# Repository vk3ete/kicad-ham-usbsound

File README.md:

# kicad-ham-usbsound
Kicad soundcard for ICOM 7100 breakboard

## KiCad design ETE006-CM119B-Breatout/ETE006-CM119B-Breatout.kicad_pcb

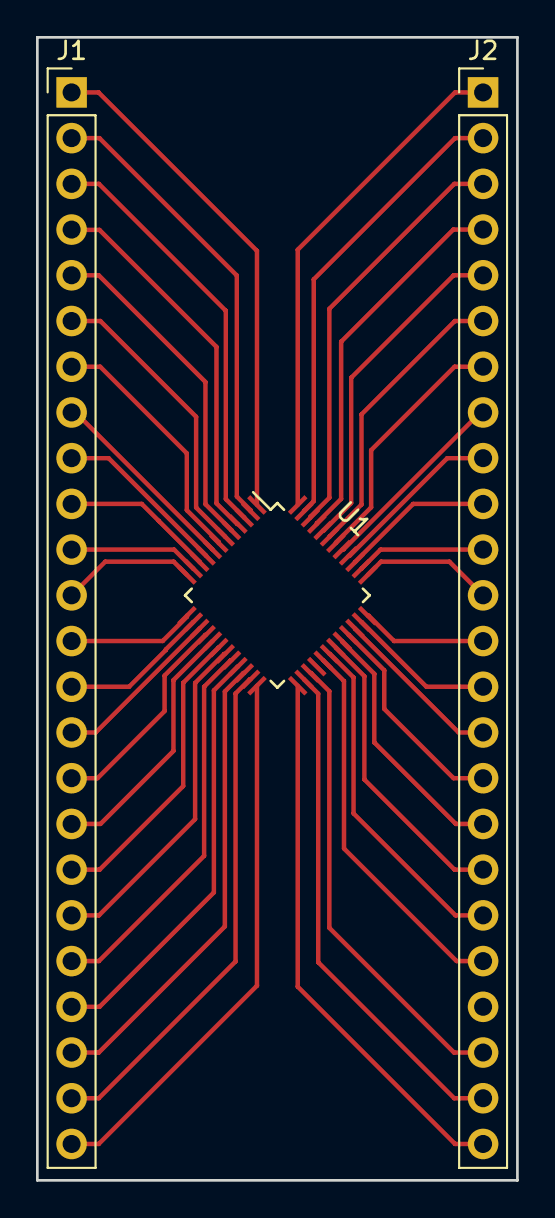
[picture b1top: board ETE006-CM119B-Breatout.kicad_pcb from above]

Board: 2 copper layers, 26.7 x 63.5 mm, 3 parts (0 on the bottom side), 47 nets.

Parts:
J1, J2: Conn_01x24_Male; PinHeader_1x24_P2.54mm_Vertical
U1: CM119B; LQFP-48_7x7mm_Pitch0.5mm

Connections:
AREG36: J2.12, U1.37
AVDD_1: J2.15, U1.34
AVDD_2: J2.20, U1.29
AVSS_1: J1.24, U1.24
AVSS_2: J2.16, U1.33
BUZZ: J1.19, U1.19
DREG18: J1.8, U1.8
DREG33: J1.9, U1.9
DVDD: J2.14, U1.35
DVSS_1: J1.14, U1.14
DVSS_2: J2.13, U1.36
D_IN: J1.2, U1.2
D_OUT: J1.3, U1.3
GPIO1: J2.6, U1.43
GPIO2: J1.11, U1.11
GPIO3: J1.13, U1.13
GPIO4: J1.15, U1.15
GPIO5: J1.16, U1.16
GPIO6: J1.17, U1.17
GPIO7: J1.20, U1.20
GPIO8: J1.22, U1.22
LED_O: J1.12, U1.12
LED_R: J1.21, U1.21
LO_BIAS: J2.18, U1.31
LO_LEFT: J2.19, U1.30
LO_RIGHT: J2.17, U1.32
MCLK: J2.2, U1.47
MIC_IN: J2.22, U1.27
MINT: J2.4, U1.45
MODE: J1.10, U1.10
MSEL: J2.11, U1.38
MUTE_PLAY: J1.18, U1.18
MUTE_REC: J1.6, U1.6
PDSW: J2.9, U1.40
PWRSEL: J1.7, U1.7
SCLK: J2.5, U1.44
SDAT: J2.3, U1.46
SK: J1.4, U1.4
SPDIFO: J1.1, U1.1
TEST: J1.23, U1.23
USB_D+: J2.8, U1.41
USB_D-: J2.7, U1.42
VBIAS: J2.24, U1.25
VOL_DN: J2.1, U1.48
VOL_UP: J2.10, U1.39
VREF: J2.23, U1.26
~CS: J1.5, U1.5

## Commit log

2019-04-20 Establish project for usb aubio breakout board
2019-04-21 Added breadboard breakout design for CM119A chip
2019-04-21 Remove apple files
2019-04-21 removing Apple files
